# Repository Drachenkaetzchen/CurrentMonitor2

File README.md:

Design Goals
============

The measurement limits are:
0-60V with 1mV resolution
0-30A with 1mA resolution

Power Input
===========

We accept two different power sources: Power from the device under test and an external power supply.

To reduce the part count we're using the LM2591HV simple switcher for powering via the device under test
or via an external power supply and an LTC4412 to switch over between the 5V rails.

Having two step-down DC converters might seem to be overkill, but I wasn't able to find an easy power
switching device which supports up to 60V which is required for the measurement input, so switching
two separate 5V rails seems to be convinient for now.

Drawbacks
=========

- We will have marginally wrong readings if powering the meter via the device under test. This needs to
  be fixed, because our current draw isn't constant (especially with the WiFi module).

Shunt Resistor Considerations
=============================

The full-scale output of the shunt resistor must be between 50mV and 100mV for optimal performance. For
30A and 0.1V voltage drop, this gives us:

R=U/I
R=0.1/30
R=0.003 (nearest value)

Dale WSL3637 was chosen due to the low cost and eagle library availability.

Cable Connector Considerations
==============================

The Connector needs to widthstand 30A, and the Phoenix Contact MKDS 5/ 2-6,35 can support up to 32A.

LCD
===
For the initial design, we're using an industry standard LCD. I'm not sure how well this works and how
interchangeable different LCDs are, or if I need to stick to a specific manufacturer.

modbus rs485?
rtc?

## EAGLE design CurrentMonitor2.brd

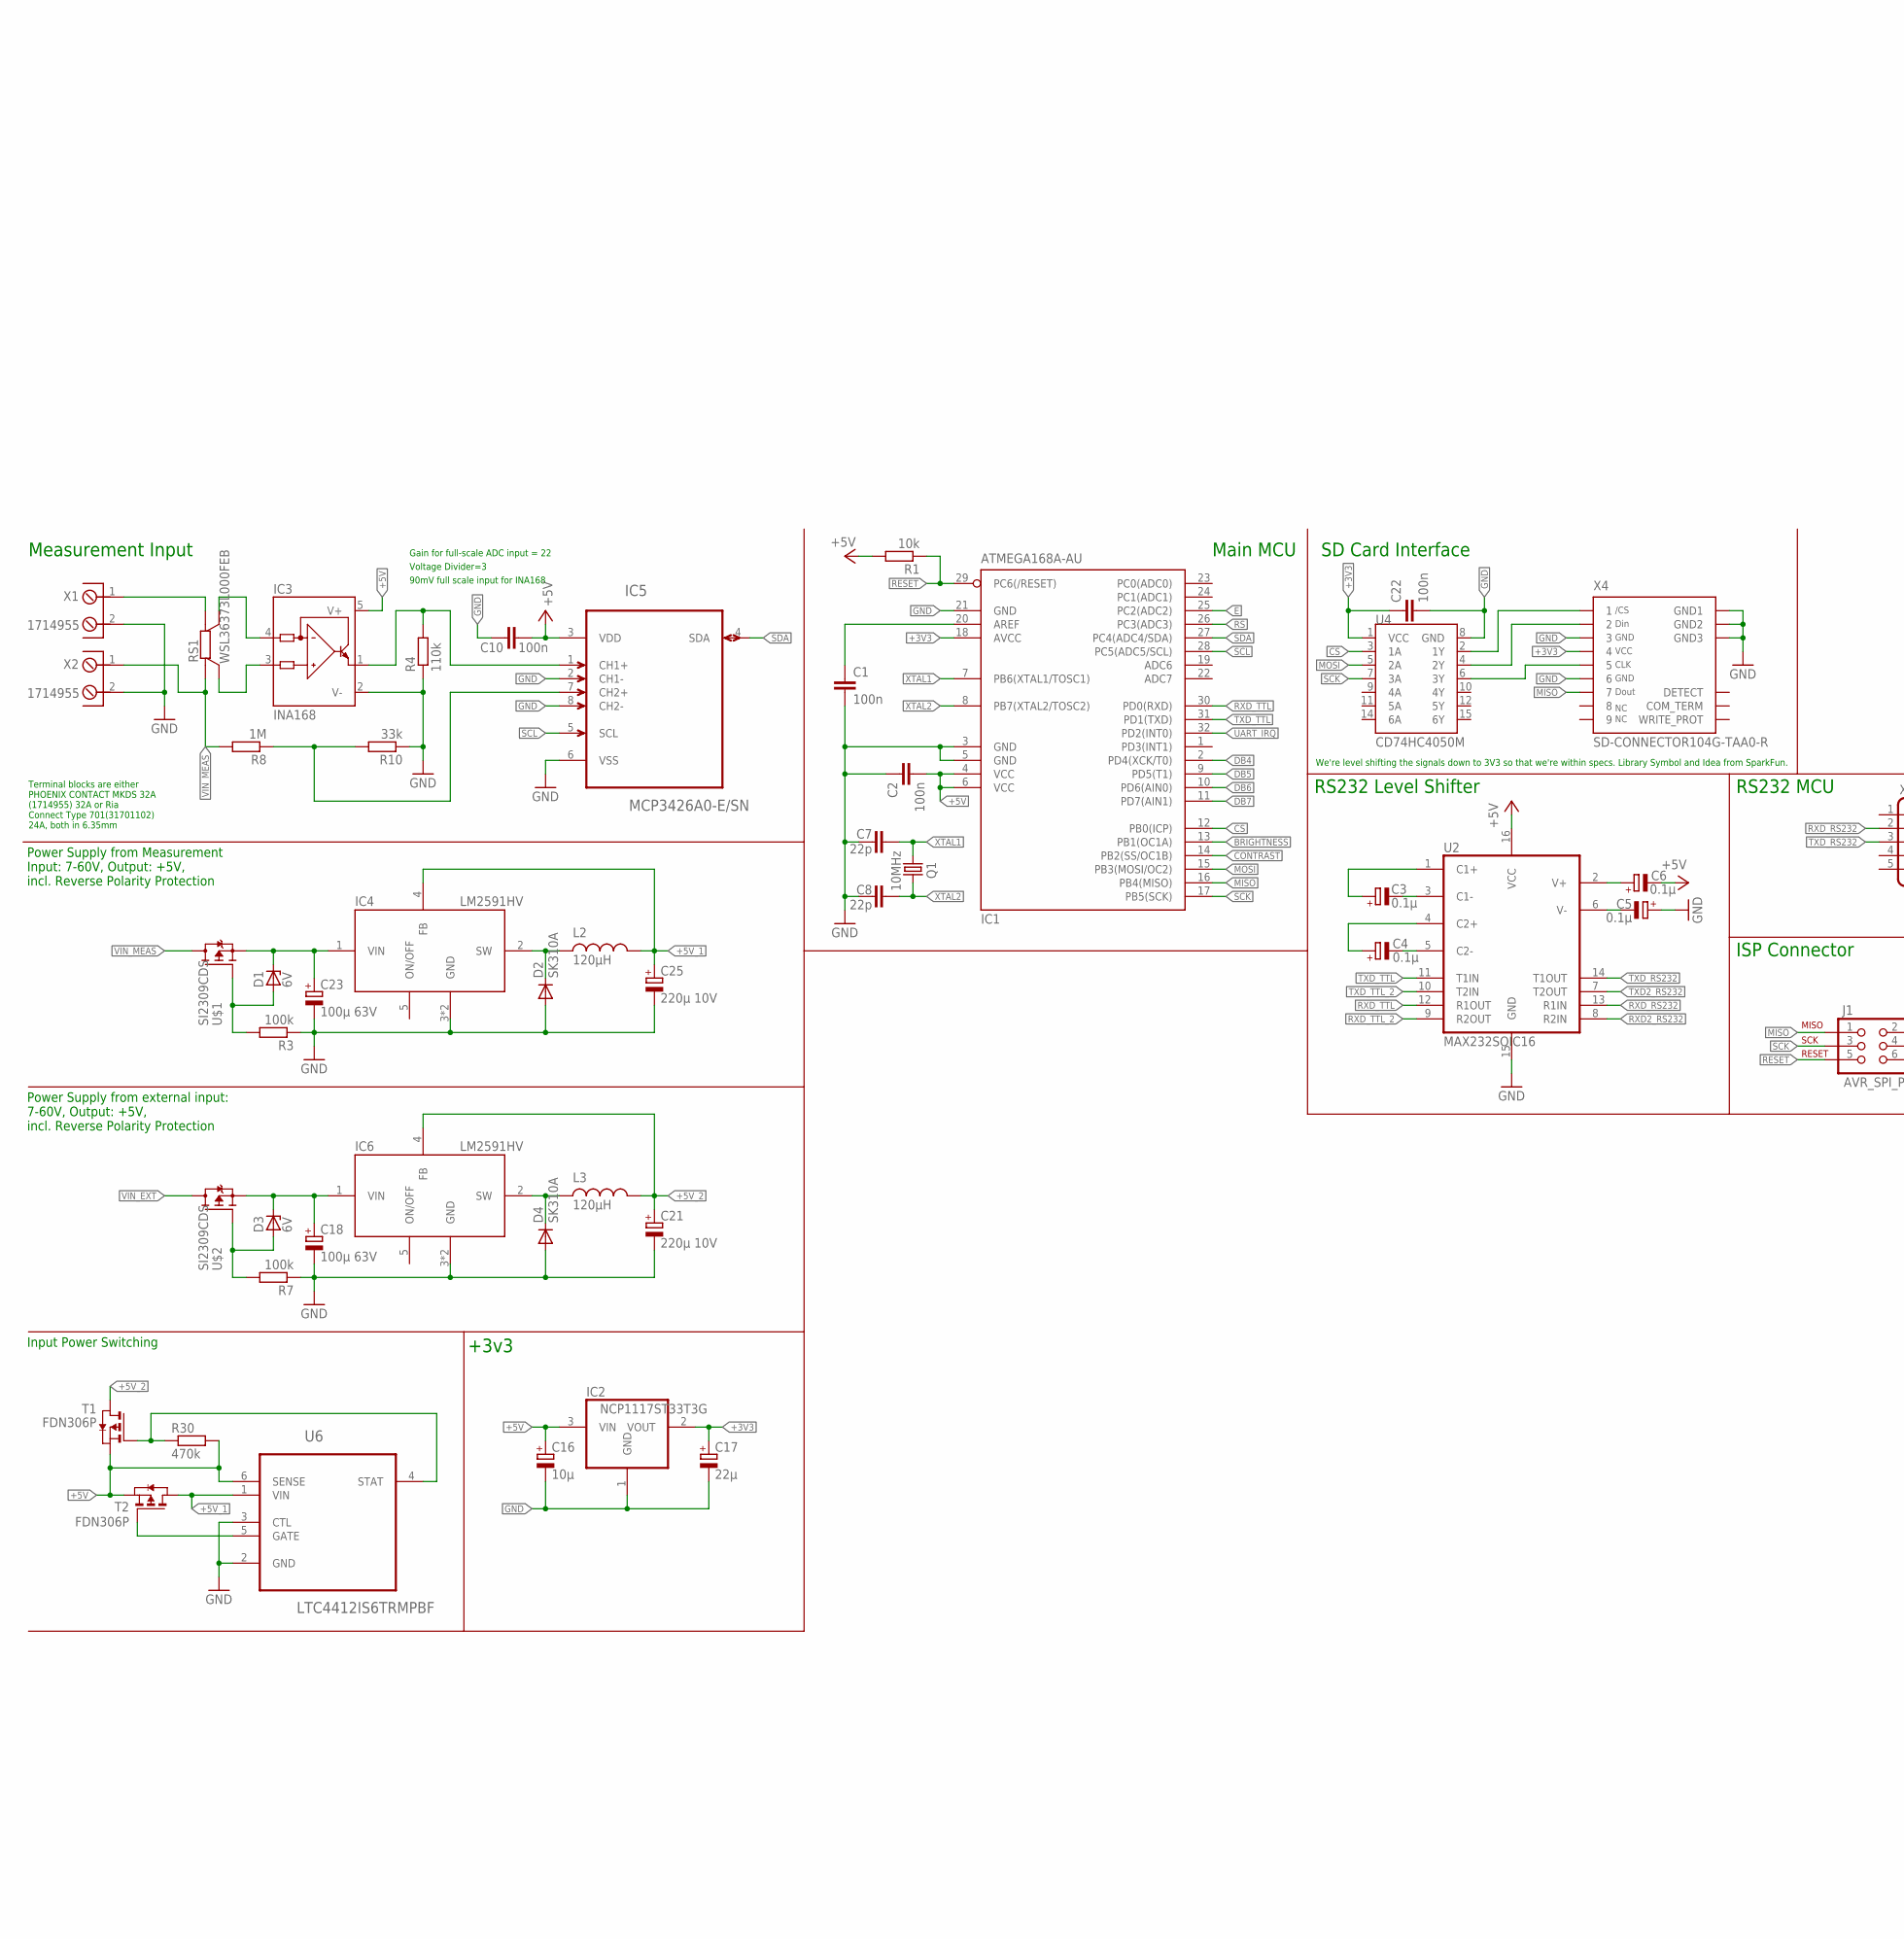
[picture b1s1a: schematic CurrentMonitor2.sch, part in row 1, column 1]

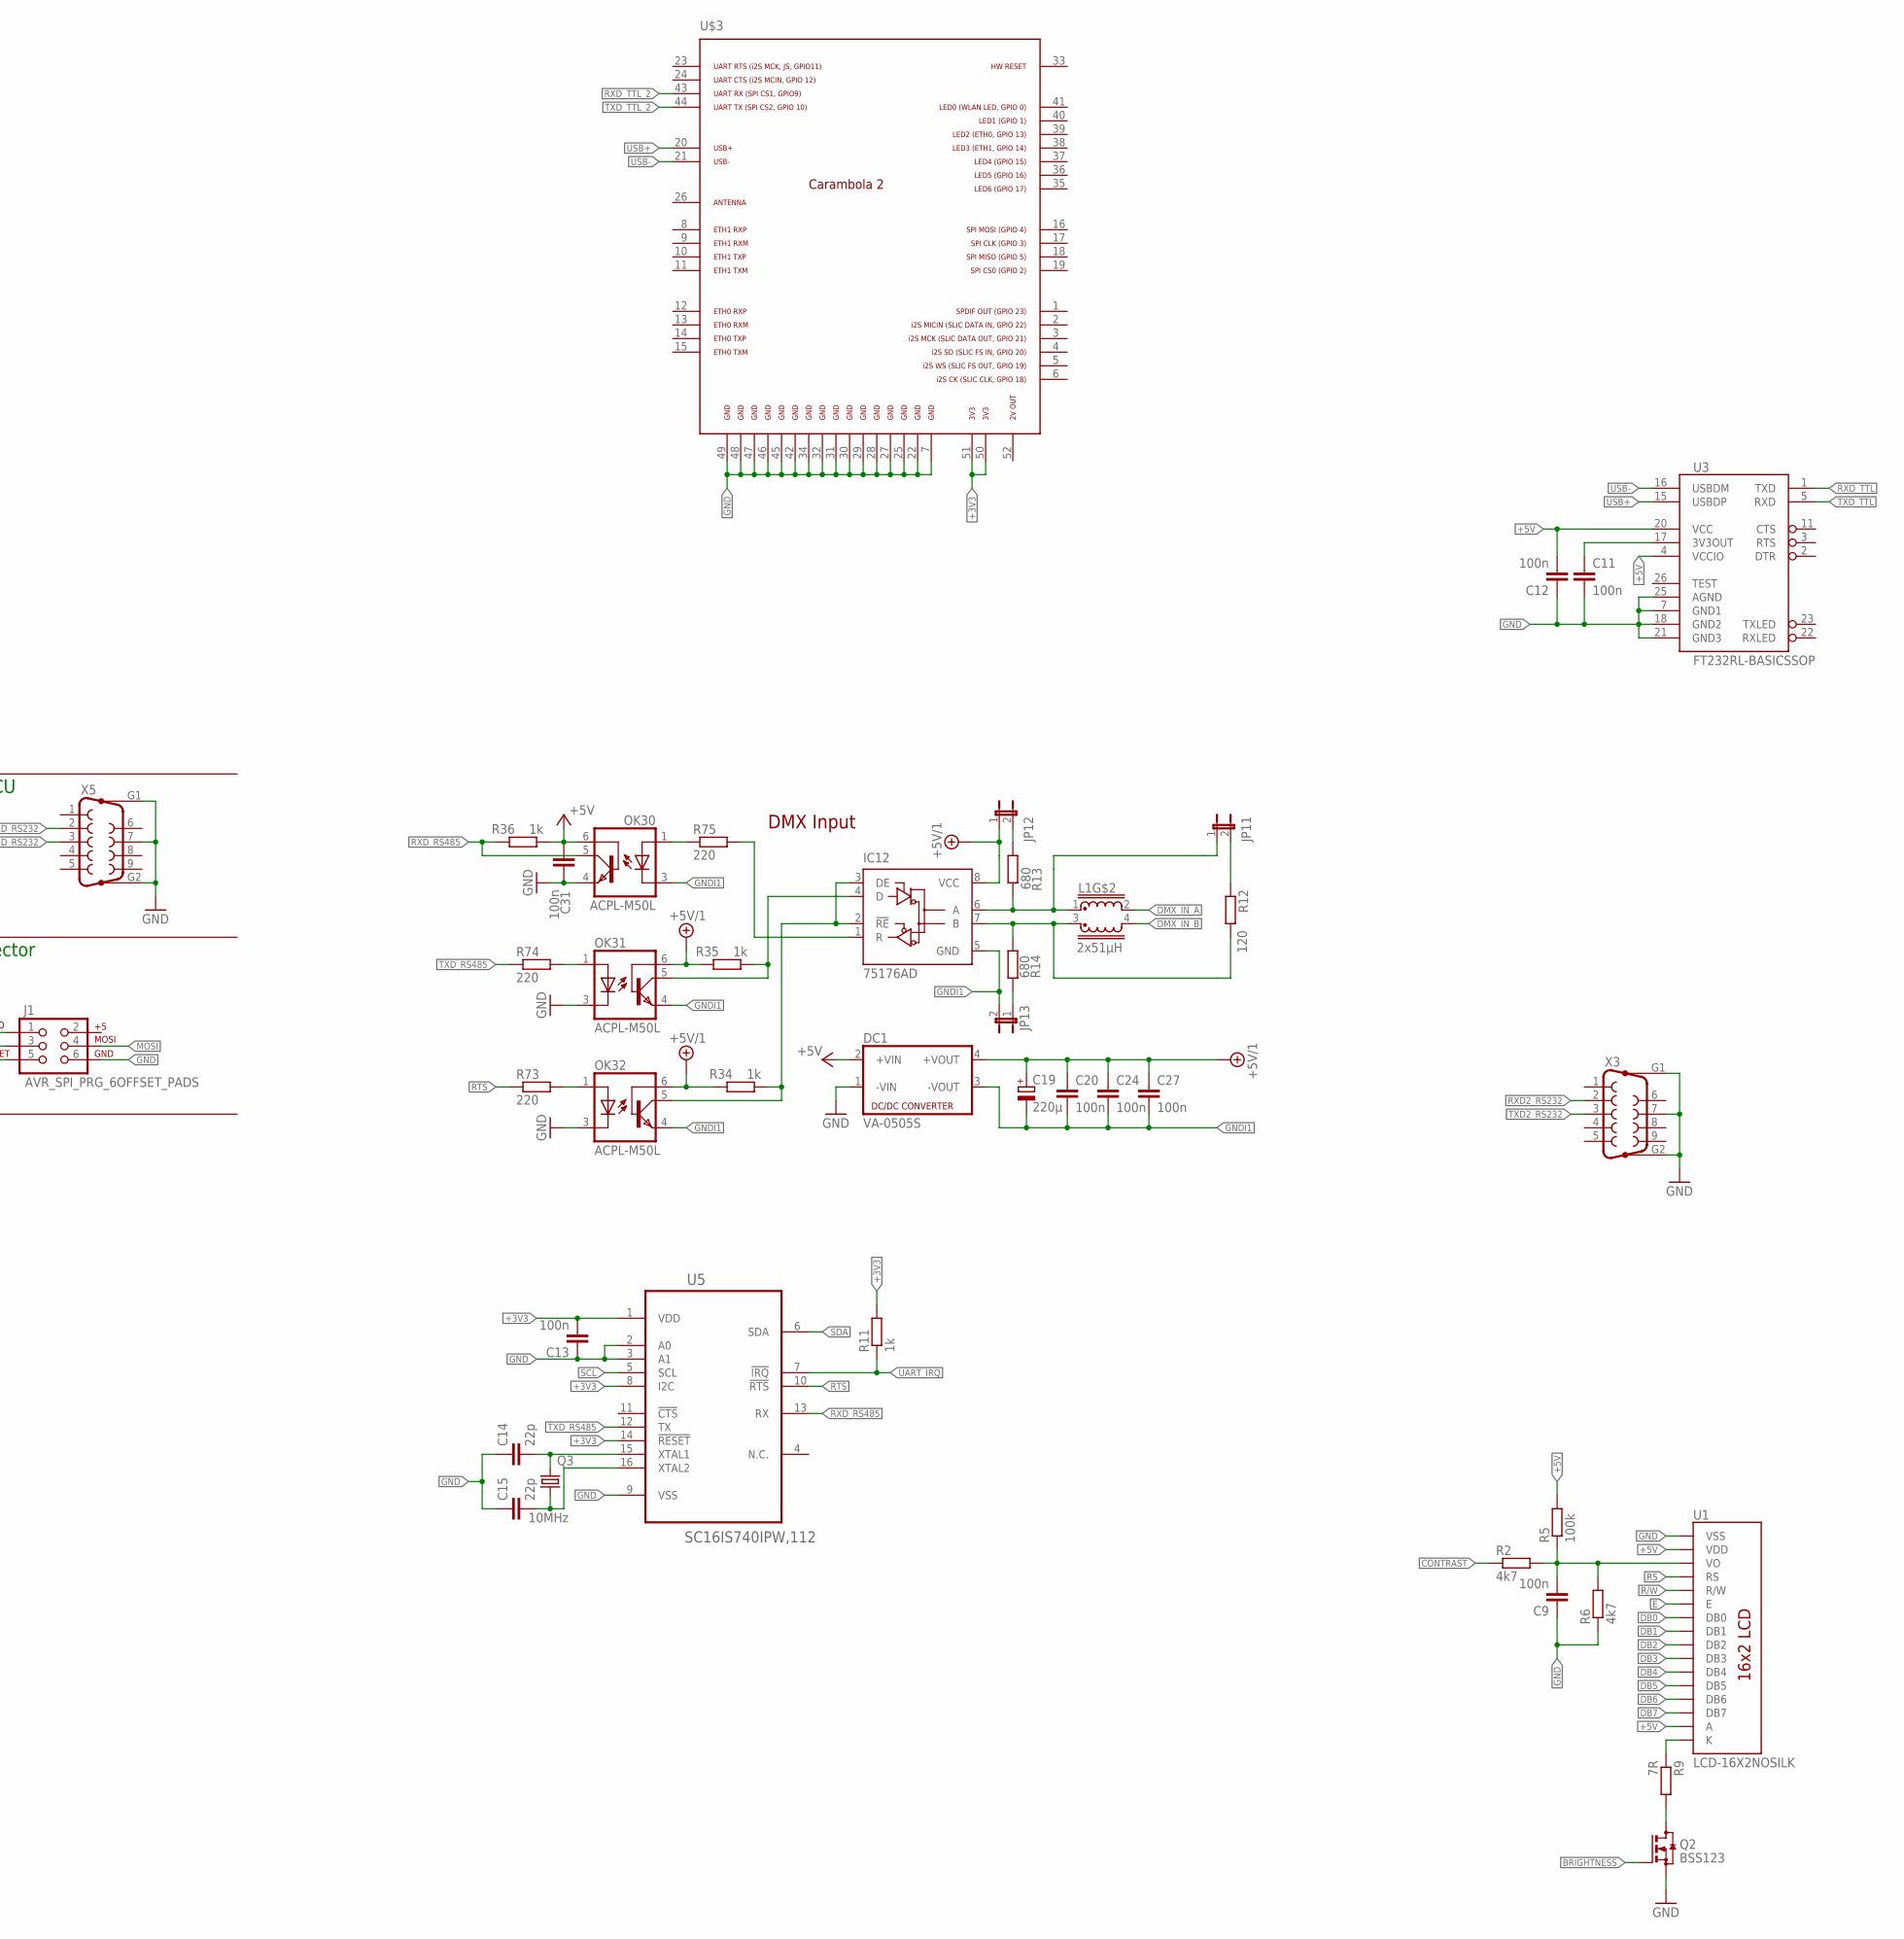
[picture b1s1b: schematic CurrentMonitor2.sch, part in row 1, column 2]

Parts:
C1, C2, C9, C10, C11, C12, C13, C20, C22, C24, C27, C31: 100n; C0805
C3, C4, C5, C6: 0.1µ; PANASONIC_B
C7, C8, C14, C15: 22p; C0805
C16: 10µ; PANASONIC_B
C17: 22µ; PANASONIC_B
C18, C23: 100µ 63V; PANASONIC_G
C19: 220µ; PANASONIC_D
C21, C25: 220µ 10V; PANASONIC_D
D1, D3: 6V; SOT23
D2, D4: SK310A; DO214AC
DC1: VA-0505S; 4SIL
IC1: ATMEGA168A-AU; TQFP32-08
IC2: NCP1117ST33T3G; SOT223
IC3: INA168; SOT23-5
IC4, IC6: LM2591HV; TO263-5
IC5: MCP3426A0-E/SN; SOIC127P600X175-8N
IC12: 75176AD; D_R-PDSO-G8
J1: AVR_SPI_PRG_6OFFSET_PADS; 2X3_OFFSET
JP11, JP12, JP13: JP1E; JP1
L1: 2x51µH; EPCOS_B82790_SERIES
L2, L3: 120µH; MSS1260
OK30, OK31, OK32: ACPL-M50L; JEDEC_MS-012-AA_SOIC5
Q1, Q3: 10MHz; HC49UP
Q2: BSS123; SOT23
R1: 10k; R0805
R2, R6: 4k7; R0805
R3, R5, R7: 100k; R0805
R4: 110k; R0805
R8: 1M; R0805
R9: 7R; R0805
R10: 33k; R0805
R11, R34, R35, R36: 1k; R0805
R12: 120; R0805
R13, R14: 680; R0805
R30: 470k; R0805
R73, R74, R75: 220; R0805
RS1: WSL36373L000FEB; CSM3637M
T1, T2: FDN306P; SOT-23
U1: LCD-16X2NOSILK; LCD-16X2_NOSILK
U2: MAX232SOIC16; SO016
U3: FT232RL-BASICSSOP; SSOP28DB
U4: CD74HC4050M; SO016
U5: SC16IS740IPW,112; SOP65P640X110-16N
U6: LTC4412IS6TRMPBF; SOT95P280X100-6N
U$1, U$2: SI2309CDS; SOT23
U$3: CARAMBOLA2
X1, X2: 1714955; AKL701_2_13
X3, X5: F09HP
X4: SD-CONNECTOR104G-TAA0-R; 104G-TAA0-R

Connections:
+3V3: C1.1, C13.2, C17.+, C22.1, IC1.18 (AVCC), IC1.20 (AREF), IC2.2 (VOUT), R11.2, U4.1 (VCC), U5.1 (VDD), U5.8 (I2C), U5.14 (!RESET), U$3.50, U$3.51, X4.4
+5V: C2.2, C6.-, C10.1, C12.2, C16.+, C31.1, DC1.2 (+VIN), IC1.4 (VCC), IC1.6 (VCC), IC2.3 (VIN), IC3.5 (V+), IC5.3 (VDD), OK30.6 (BAS), R1.2, R5.2, R30.2, R36.1, T1.2 (S), T2.2 (S), U1.2 (VDD), U1.15 (A), U2.16 (VCC), U3.4 (VCCIO), U3.20 (VCC), U6.6 (SENSE)
+5V_1: C25.+, IC4.4 (FB), L2.P$1, T2.1 (D), U6.1 (VIN)
+5V_2: C21.+, IC6.4 (FB), L3.P$1, T1.1 (D)
ADC0: IC3.1 (OUT), IC5.1 (CH1+), R4.2
ADC1: IC5.7 (CH2+), R8.1, R10.2
BRIGHTNESS: IC1.13 (PB1(OC1A)), Q2.1 (G)
CONTRAST: IC1.14 (PB2(SS/OC1B)), R2.1
CS: IC1.12 (PB0(ICP)), U4.3 (1A)
DB0: U1.7 (DB0)
DB1: U1.8 (DB1)
DB2: U1.9 (DB2)
DB3: U1.10 (DB3)
DB4: IC1.2 (PD4(XCK/T0)), U1.11 (DB4)
DB5: IC1.9 (PD5(T1)), U1.12 (DB5)
DB6: IC1.10 (PD6(AIN0)), U1.13 (DB6)
DB7: IC1.11 (PD7(AIN1)), U1.14 (DB7)
DMX_IN_A: L1.2 (4)
DMX_IN_B: L1.4
E: IC1.25 (PC2(ADC2)), U1.6 (E)
GND: C1.2, C2.1, C5.+, C7.1, C8.1, C9.1, C10.2, C11.2, C12.1, C13.1, C14.1, C15.1, C16.-, C17.-, C18.-, C21.-, C22.2, C23.-, C25.-, C31.2, D2.A, D4.A, DC1.1 (-VIN), IC1.3 (GND), IC1.5 (GND), IC1.21 (GND), IC2.1 (GND), IC3.2 (V-), IC4.3 (GND), IC4.6 (GND), IC5.2 (CH1-), IC5.6 (VSS), IC5.8 (CH2-), IC6.3 (GND), IC6.6 (GND), J1.6, OK30.4 (EMI), OK31.3 (C), OK32.3 (C), Q2.2 (S), R3.1, R4.1, R6.1, R7.1, R10.1, U1.1 (VSS), U2.15 (GND), U3.7 (GND1), U3.18 (GND2), U3.21 (GND3), U3.25 (AGND), U4.8 (GND), U5.2 (A0), U5.3 (A1), U5.9 (VSS), U6.2 (GND), U6.3 (CTL), U$3.7, U$3.22, U$3.25, U$3.27, U$3.28, U$3.29, U$3.30, U$3.31, U$3.32, U$3.34, U$3.42, U$3.45, U$3.46, U$3.47, U$3.48, U$3.49, X1.2, X2.2, X3.7, X3.G1, X3.G2, X4.3, X4.6, X4.GND1, X4.GND2, X4.GND3, X5.7, X5.G1, X5.G2
GNDI1: C19.-, C20.2, C24.2, C27.2, DC1.3 (-VOUT), IC12.5 (GND), JP13.2, OK30.3 (C), OK31.4 (EMI), OK32.4 (EMI)
MISO: IC1.16 (PB4(MISO)), J1.1, X4.7
MOSI: IC1.15 (PB3(MOSI/OC2)), J1.4, U4.5 (2A)
unnamed: IC3.3 (IN+), RS1.S2
unnamed: IC3.4 (IN-), RS1.S1
unnamed: D3.1 (A), R7.2, U$2.1 (G)
unnamed: D1.1 (A), R3.2, U$1.1 (G)
unnamed: RS1.I1, X1.1
unnamed: C6.+, U2.2 (V+)
unnamed: D4.C, IC6.2 (SW), L3.P$2
unnamed: R30.1, T1.3 (G), U6.4 (STAT)
unnamed: C5.-, U2.6 (V-)
unnamed: D2.C, IC4.2 (SW), L2.P$2
unnamed: C3.-, U2.3 (C1-)
unnamed: C4.-, U2.5 (C2-)
unnamed: C4.+, U2.4 (C2+)
unnamed: C3.+, U2.1 (C1+)
unnamed: T2.3 (G), U6.5 (GATE)
unnamed: Q2.3 (D), R9.2
unnamed: C11.1, U3.17 (3V3OUT)
unnamed: C14.2, Q3.2, U5.15 (XTAL1)
unnamed: C15.2, Q3.1, U5.16 (XTAL2)
unnamed: U4.2 (1Y), X4.1
unnamed: U4.4 (2Y), X4.2
unnamed: R9.1, U1.16 (K)
unnamed: U4.6 (3Y), X4.5
unnamed: IC12.6 (A), JP11.1, L1.1, R13.1
unnamed: JP12.2, R13.2
unnamed: JP13.1, R14.1
unnamed: JP11.2, R12.1
unnamed: IC12.7 (B), L1.3 (1), R12.2, R14.2
unnamed: OK30.1 (A), R75.1
unnamed: OK31.1 (A), R74.2
unnamed: OK32.1 (A), R73.2
R/W: U1.5 (R/W)
REC$1: IC12.1 (R), R75.2
RESET: IC1.29 (PC6(/RESET)), J1.5, R1.1
RE_OUT: IC12.2 (!RE), IC12.3 (DE), OK32.5 (COL), R34.1
RS: IC1.26 (PC3(ADC3)), U1.4 (RS)
RTS: R73.1, U5.10 (!RTS)
RXD2_RS232: U2.8 (R2IN), X3.2
RXD_RS232: U2.13 (R1IN), X5.2
RXD_RS485: OK30.5 (COL), R36.2, U5.13 (RX)
RXD_TTL: IC1.30 (PD0(RXD)), U2.12 (R1OUT), U3.1 (TXD)
RXD_TTL_2: U2.9 (R2OUT), U$3.43
SCK: IC1.17 (PB5(SCK)), J1.3, U4.7 (3A)
SCL: IC1.28 (PC5(ADC5/SCL)), IC5.5 (SCL), U5.5 (SCL)
SDA: IC1.27 (PC4(ADC4/SDA)), IC5.4 (SDA), U5.6 (SDA)
TXD2_RS232: U2.7 (T2OUT), X3.3
TXD_OUT: IC12.4 (D), OK31.5 (COL), R35.1
TXD_RS232: U2.14 (T1OUT), X5.3
TXD_RS485: R74.1, U5.12 (TX)
TXD_TTL: IC1.31 (PD1(TXD)), U2.11 (T1IN), U3.5 (RXD)
TXD_TTL_2: U2.10 (T2IN), U$3.44
UART_IRQ: IC1.32 (PD2(INT0)), R11.1, U5.7 (!IRQ)
USB+: U3.15 (USBDP), U$3.20
USB-: U3.16 (USBDM), U$3.21
VCCIO1: C19.+, C20.1, C24.1, C27.1, DC1.4 (+VOUT), IC12.8 (VCC), JP12.1, OK31.6 (BAS), OK32.6 (BAS), R34.2, R35.2
VIN: C23.+, D1.3 (C), IC4.1 (VIN), U$1.2 (S)
VIN1: C18.+, D3.3 (C), IC6.1 (VIN), U$2.2 (S)
VIN_EXT: U$2.3 (D)
VIN_MEAS: R8.2, RS1.I2, U$1.3 (D), X2.1
VO: C9.2, R2.2, R5.1, R6.2, U1.3 (VO)
XTAL1: C7.2, IC1.7 (PB6(XTAL1/TOSC1)), Q1.2
XTAL2: C8.2, IC1.8 (PB7(XTAL2/TOSC2)), Q1.1

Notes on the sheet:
Gain for full-scale ADC input = 22
Voltage Divider=3
Terminal blocks are either PHOENIX CONTACT MKDS 32A (1714955) 32A or Ria Connect Type 701(31701102) 24A, both in 6.35mm
90mV full scale input for INA168
DMX Input
Measurement Input
Main MCU
SD Card Interface
We're level shifting the signals down to 3V3 so that we're within specs. Library Symbol and Idea from SparkFun.
RS232 Level Shifter
RS232 MCU
ISP Connector
+3v3
Power Supply from Measurement Input: 7-60V, Output: +5V, incl. Reverse Polarity Protection
Power Supply from external input: 7-60V, Output: +5V, incl. Reverse Polarity Protection
Input Power Switching

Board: 2 copper layers, 90 parts (0 on the bottom side), 78 nets, no tracks yet.

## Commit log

2013-08-06 Added RS485 and WiFi options, finalized some parts of the design including order codes and prices @100pcs
2013-08-07 Added dual input switching power supplies and power switching circuitry

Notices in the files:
parts and their libraries:
SparkFun: Licensing: CC v3.0 Share-Alike You are welcome to use this library for commercial purposes.
